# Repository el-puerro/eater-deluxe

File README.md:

# eater-deluxe - a retro computer from the modern times

A 6502-based personal computer with 32K of SRAM, an LCD Display and
an RS232 Serial interface, based on [Ben Eater's 6502 Breadboard Computer](https://eater.net/6502)

It is compatible with all software running on the breadboard 6502 computer.

## Dependencies for the KiCAD Project

[6502 KiCAD Library](https://github.com/Alarm-Siren/6502-kicad-library)

## Errata

### Revision 1.0

- The clock pinout is messed up. If you already have a revision 1.0 board, solder
  single pin headers in to make it easier to connect up the clock can
- LCD footprint is too small. You can still try to solder in some wires, but this
  was initially intended for pin headers, so your mileage may vary.
- Interrupt lines are missing pullup resistors. Should still work unmodified if
  you don't use these, otherwise you need to wire botch wires instead.

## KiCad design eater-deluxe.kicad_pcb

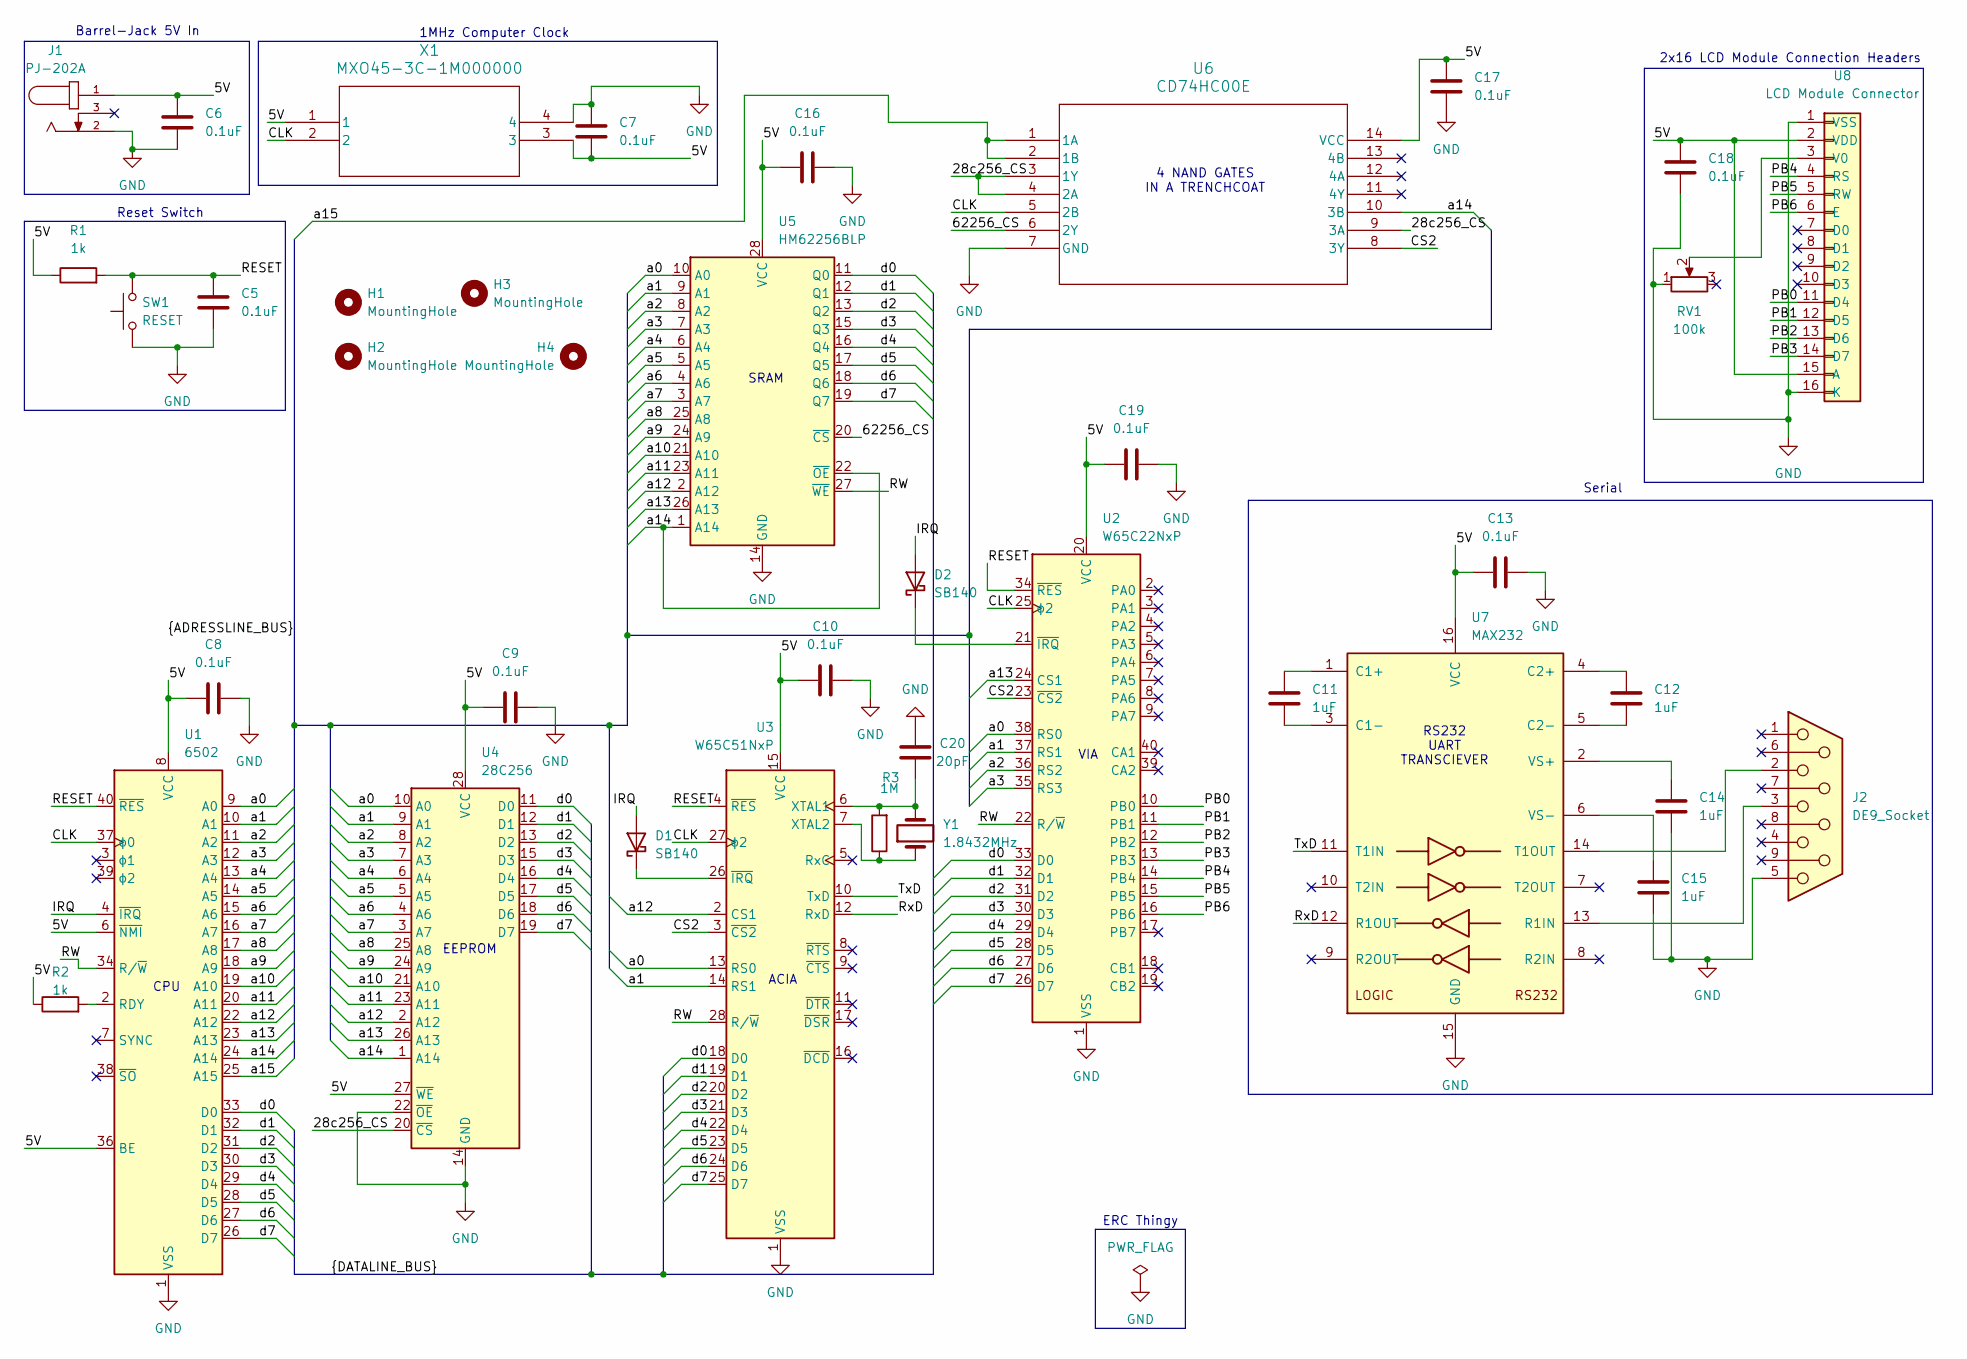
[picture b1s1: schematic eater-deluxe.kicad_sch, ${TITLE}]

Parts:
C5, C6, C7, C8, C9, C10, C13, C16, C17, C18, C19: 0.1uF; C_Axial_L12.0mm_D6.5mm_P15.00mm_Horizontal
C11, C12, C14, C15: 1uF; C_Axial_L12.0mm_D6.5mm_P15.00mm_Horizontal
C20: 20pF; C_Axial_L12.0mm_D6.5mm_P15.00mm_Horizontal
D1, D2: SB140; D_DO-41_SOD81_P10.16mm_Horizontal
H1, H2, H3, H4: MountingHole; MountingHole_3.2mm_M3
J1: PJ-202A; CUI_PJ-202A
J2: DE9_Socket; DSUB-9_Socket_Horizontal_P2.77x2.54mm_EdgePinOffset9.40mm
R1, R2: 1k; R_Axial_DIN0204_L3.6mm_D1.6mm_P7.62mm_Horizontal
R3: 1M; R_Axial_DIN0204_L3.6mm_D1.6mm_P7.62mm_Horizontal
RV1: 100k; Potentiometer_ACP_CA14-H2,5_Horizontal
SW1: RESET; SW_PUSH-12mm
U1: 6502; DIP-40_W15.24mm_Socket
U2: W65C22NxP; DIP-40_W15.24mm_Socket
U3: W65C51NxP; DIP-28_W15.24mm_Socket
U4: 28C256; DIP-28_W15.24mm_Socket
U5: HM62256BLP; DIP-28_W15.24mm_Socket
U6: CD74HC00E; N14
U7: MAX232; DIP-16_W7.62mm_Socket
U8: LCD Module Connector; PinHeader_1x16_P1.00mm_Horizontal
X1: MXO45-3C-1M000000; DIP4_MXO45-3C-1M000000_CTS
Y1: 1.8432MHz; Crystal_HC49-U_Vertical

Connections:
/5V: C6.2, C7.1, C8.1, C9.1, C10.1, C13.1, C16.1, C17.2, C18.2, C19.1, J1.1, R1.1, R2.1, U1.6 (~NMI), U1.8 (VCC), U1.36 (BE), U2.20 (VCC), U3.15 (VCC), U4.27 (~WE), U4.28 (VCC), U5.28 (VCC), U6.14 (VCC), U7.16 (VCC), U8.2 (VDD), U8.15 (A), X1.1, X1.3
/28c256_CS: U4.20 (~CS), U6.3 (1Y), U6.4 (2A), U6.9 (3A)
/62256_CS: U5.20 (~CS), U6.6 (2Y)
/CLK: U1.37 (ϕ0), U2.25 (ϕ2), U3.27 (ϕ2), U6.5 (2B), X1.2
/CS2: U2.23 (~CS2), U3.3 (~CS2), U6.8 (3Y)
/IRQ: D1.2 (A), D2.2 (A), U1.4 (~IRQ)
/PB0: U2.10 (PB0), U8.11 (D4)
/PB1: U2.11 (PB1), U8.12 (D5)
/PB2: U2.12 (PB2), U8.13 (D6)
/PB3: U2.13 (PB3), U8.14 (D7)
/PB4: U2.14 (PB4), U8.4 (RS)
/PB5: U2.15 (PB5), U8.5 (RW)
/PB6: U2.16 (PB6), U8.6 (E)
/RESET: C5.2, R1.2, SW1.2, U1.40 (~RES), U2.34 (~RES), U3.4 (~RES)
/RW: U1.34 (R/~W), U2.22 (R/~W), U3.28 (R/~W), U5.27 (~WE)
/RxD: U3.12 (RxD), U7.12 (R1OUT)
/TxD: U3.10 (TxD), U7.11 (T1IN)
/a0: U1.9 (A0), U2.38 (RS0), U3.13 (RS0), U4.10 (A0), U5.10 (A0)
/a1: U1.10 (A1), U2.37 (RS1), U3.14 (RS1), U4.9 (A1), U5.9 (A1)
/a2: U1.11 (A2), U2.36 (RS2), U4.8 (A2), U5.8 (A2)
/a3: U1.12 (A3), U2.35 (RS3), U4.7 (A3), U5.7 (A3)
/a4: U1.13 (A4), U4.6 (A4), U5.6 (A4)
/a5: U1.14 (A5), U4.5 (A5), U5.5 (A5)
/a6: U1.15 (A6), U4.4 (A6), U5.4 (A6)
/a7: U1.16 (A7), U4.3 (A7), U5.3 (A7)
/a8: U1.17 (A8), U4.25 (A8), U5.25 (A8)
/a9: U1.18 (A9), U4.24 (A9), U5.24 (A9)
/a10: U1.19 (A10), U4.21 (A10), U5.21 (A10)
/a11: U1.20 (A11), U4.23 (A11), U5.23 (A11)
/a12: U1.22 (A12), U3.2 (CS1), U4.2 (A12), U5.2 (A12)
/a13: U1.23 (A13), U2.24 (CS1), U4.26 (A13), U5.26 (A13)
/a14: U1.24 (A14), U4.1 (A14), U5.1 (A14), U5.22 (~OE), U6.10 (3B)
/a15: U1.25 (A15), U6.1 (1A), U6.2 (1B)
/d0: U1.33 (D0), U2.33 (D0), U3.18 (D0), U4.11 (D0), U5.11 (Q0)
/d1: U1.32 (D1), U2.32 (D1), U3.19 (D1), U4.12 (D1), U5.12 (Q1)
/d2: U1.31 (D2), U2.31 (D2), U3.20 (D2), U4.13 (D2), U5.13 (Q2)
/d3: U1.30 (D3), U2.30 (D3), U3.21 (D3), U4.15 (D3), U5.15 (Q3)
/d4: U1.29 (D4), U2.29 (D4), U3.22 (D4), U4.16 (D4), U5.16 (Q4)
/d5: U1.28 (D5), U2.28 (D5), U3.23 (D5), U4.17 (D5), U5.17 (Q5)
/d6: U1.27 (D6), U2.27 (D6), U3.24 (D6), U4.18 (D6), U5.18 (Q6)
/d7: U1.26 (D7), U2.26 (D7), U3.25 (D7), U4.19 (D7), U5.19 (Q7)
GND: C5.1, C6.1, C7.2, C8.2, C9.2, C10.2, C13.2, C14.2, C15.2, C16.2, C17.1, C18.1, C19.2, C20.2, J1.2, J2.5, RV1.1, SW1.1, U1.1 (VSS), U1.21 (VSS), U2.1 (VSS), U3.1 (VSS), U4.14 (GND), U4.22 (~OE), U5.14 (GND), U6.7 (GND), U7.15 (GND), U8.1 (VSS), U8.16 (K), X1.4
unnamed: D1.1 (K), U3.26 (~IRQ)
unnamed: D2.1 (K), U2.21 (~IRQ)
unnamed: R2.2, U1.2 (RDY)
unnamed: C20.1, R3.2, U3.6 (XTAL1), Y1.2
unnamed: R3.1, U3.7 (XTAL2), Y1.1
unnamed: C11.1, U7.1 (C1+)
unnamed: C11.2, U7.3 (C1-)
unnamed: C12.1, U7.4 (C2+)
unnamed: C12.2, U7.5 (C2-)
unnamed: J2.3, U7.13 (R1IN)
unnamed: J2.2, U7.14 (T1OUT)
unnamed: C14.1, U7.2 (VS+)
unnamed: C15.1, U7.6 (VS-)
unnamed: RV1.2, U8.3 (V0)

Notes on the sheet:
Reset Switch
1MHz Computer Clock
EEPROM
2x16 LCD Module Connection Headers
4 NAND GATES IN A TRENCHCOAT
SRAM
Serial
VIA
CPU
ERC Thingy
RS232 UART TRANSCIEVER
ACIA
Barrel-Jack 5V In

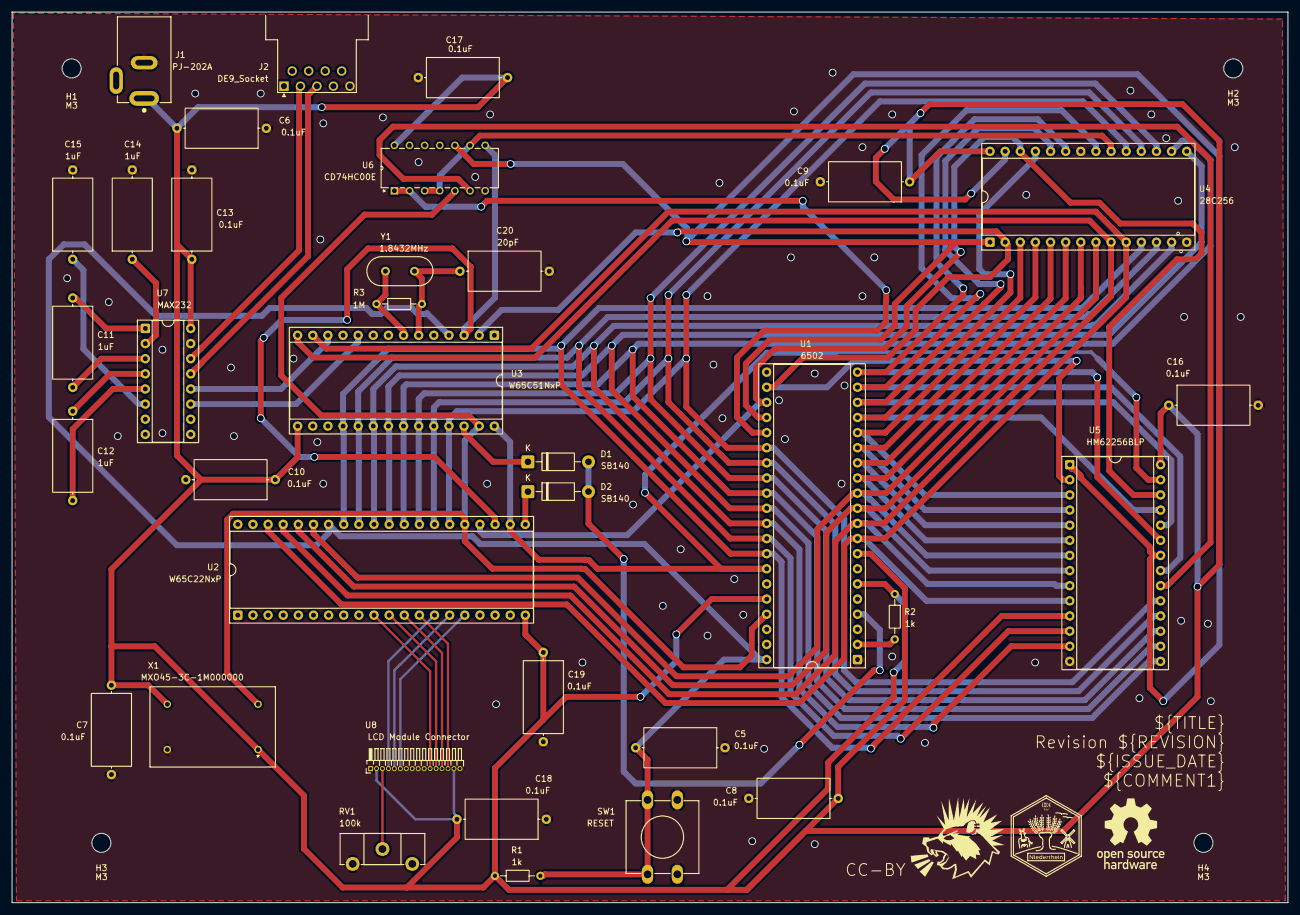
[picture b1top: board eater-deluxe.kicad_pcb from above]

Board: 2 copper layers, 214.2 x 149.5 mm, 39 parts (0 on the bottom side), 56 nets.

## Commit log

2026-05-28 init kicad project
2026-05-30 Schematic: All special components added
    All special components, that are somewhat special has been added. These
    are things like the crystal oscillator, the cpu, via, sram, eeprom, etc.
2026-05-30 README: Update dependency
2026-05-30 Schematics. Intermediate commit: only W65C22 Missing
2026-05-30 Schematics rev 1.0 finished
2026-05-30 schematics/*: Add printable/readable schematic exports
2026-05-31 PCB Layout rev1.0 finished
2026-06-01 revision 1.0 completely finished
2026-06-01 Order ready
2026-06-04 Remove starlightnet.work references
2026-06-06 README: Update description
    TODO: needs some photos and gifs as soon as i get to solder everything,
    flash the ROM, and make it go beepboop
2026-06-07 STL & pcb drawings
2026-06-14 Add license
2026-06-25 typo
2026-06-25 readme: wrong file extension
    Holy fuck this heatwave is cooking my chickenbreast-shaped brain alive

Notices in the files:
eater-deluxe.kicad_pcb:
CC-BY
